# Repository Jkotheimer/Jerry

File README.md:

# Jerry

This is Jerry. A homemade RC toy for my cats to play with. Everything in this repository encapsulates all the technologies used to make this project a reality.

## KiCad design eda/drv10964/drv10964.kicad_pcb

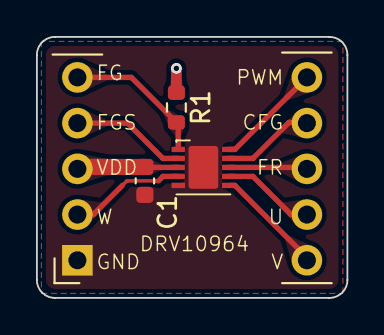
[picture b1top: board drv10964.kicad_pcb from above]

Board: 2 copper layers, 17.2 x 14.5 mm, 5 parts (0 on the bottom side), 10 nets.

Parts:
C1: 2.2uF; C_0603_1608Metric
DRV10964: drv10964
J1, J2: Conn_01x05_Pin; PinHeader_1x05_P2.54mm_Vertical
R1: 100k; R_0603_1608Metric

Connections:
/CFG: DRV10964.9 (CFG), J1.4
/FG: DRV10964.1 (FG), J2.1, R1.2
/FGS: DRV10964.2 (FGS), J2.2
/FR: DRV10964.8 (FR), J1.3
/PWM: DRV10964.10 (PWM), J1.5
/U: DRV10964.7 (U), J1.2
/V: DRV10964.6 (V), J1.1
/W: DRV10964.4 (W), J2.4
GND: C1.2, DRV10964.5 (GND), J2.5
VDD: C1.1, DRV10964.3 (VCC), J2.3, R1.1

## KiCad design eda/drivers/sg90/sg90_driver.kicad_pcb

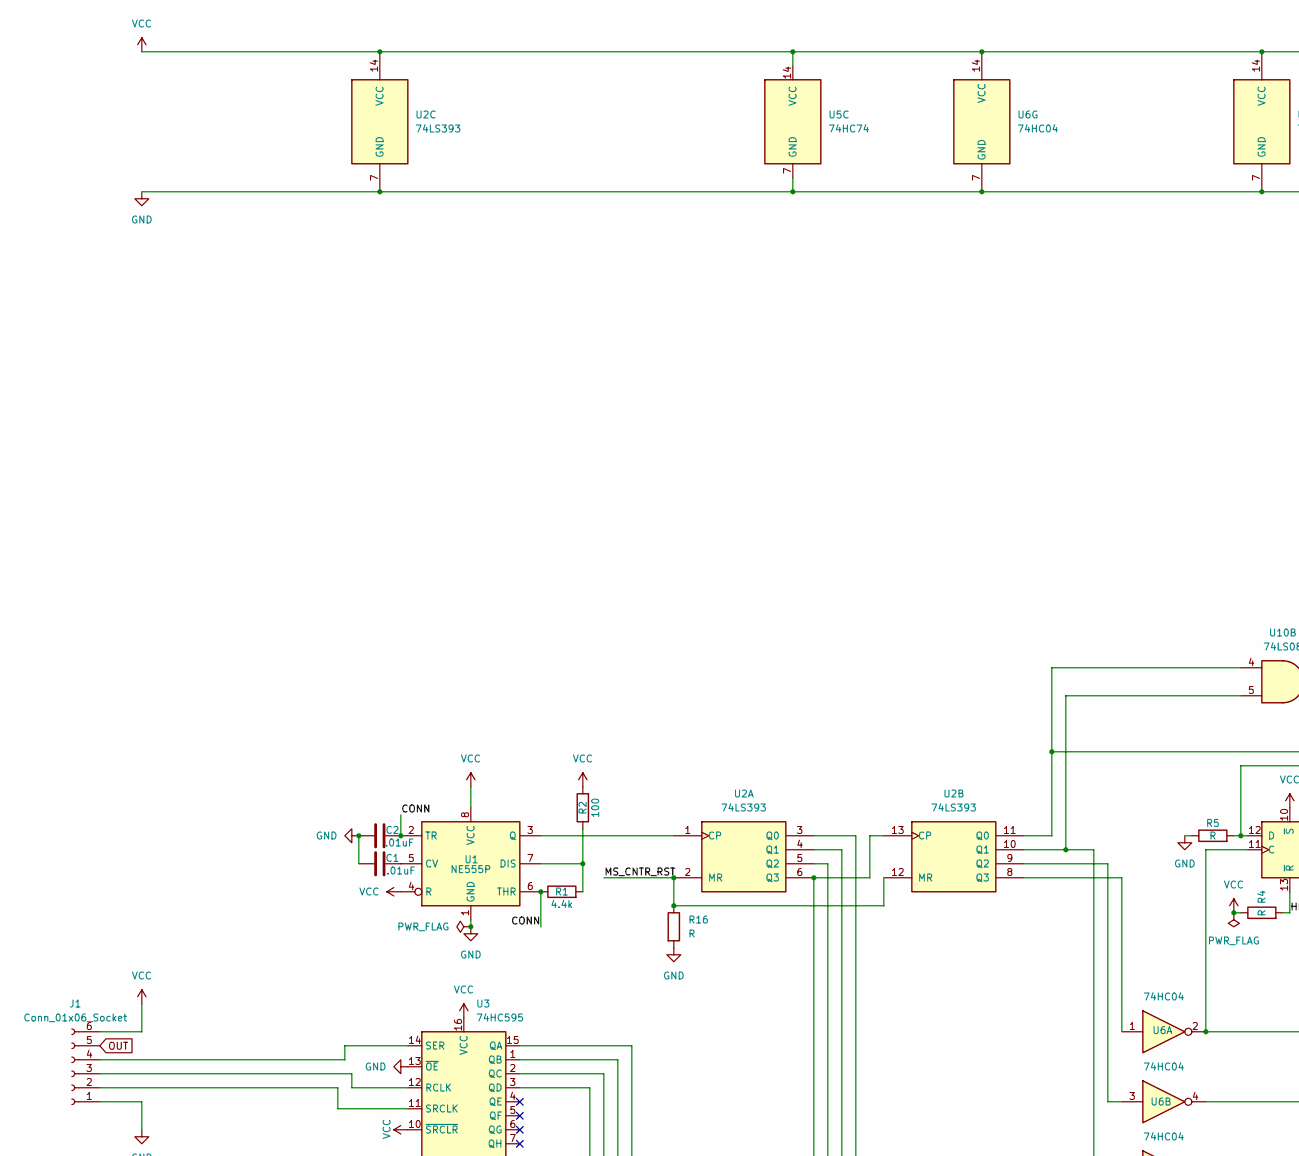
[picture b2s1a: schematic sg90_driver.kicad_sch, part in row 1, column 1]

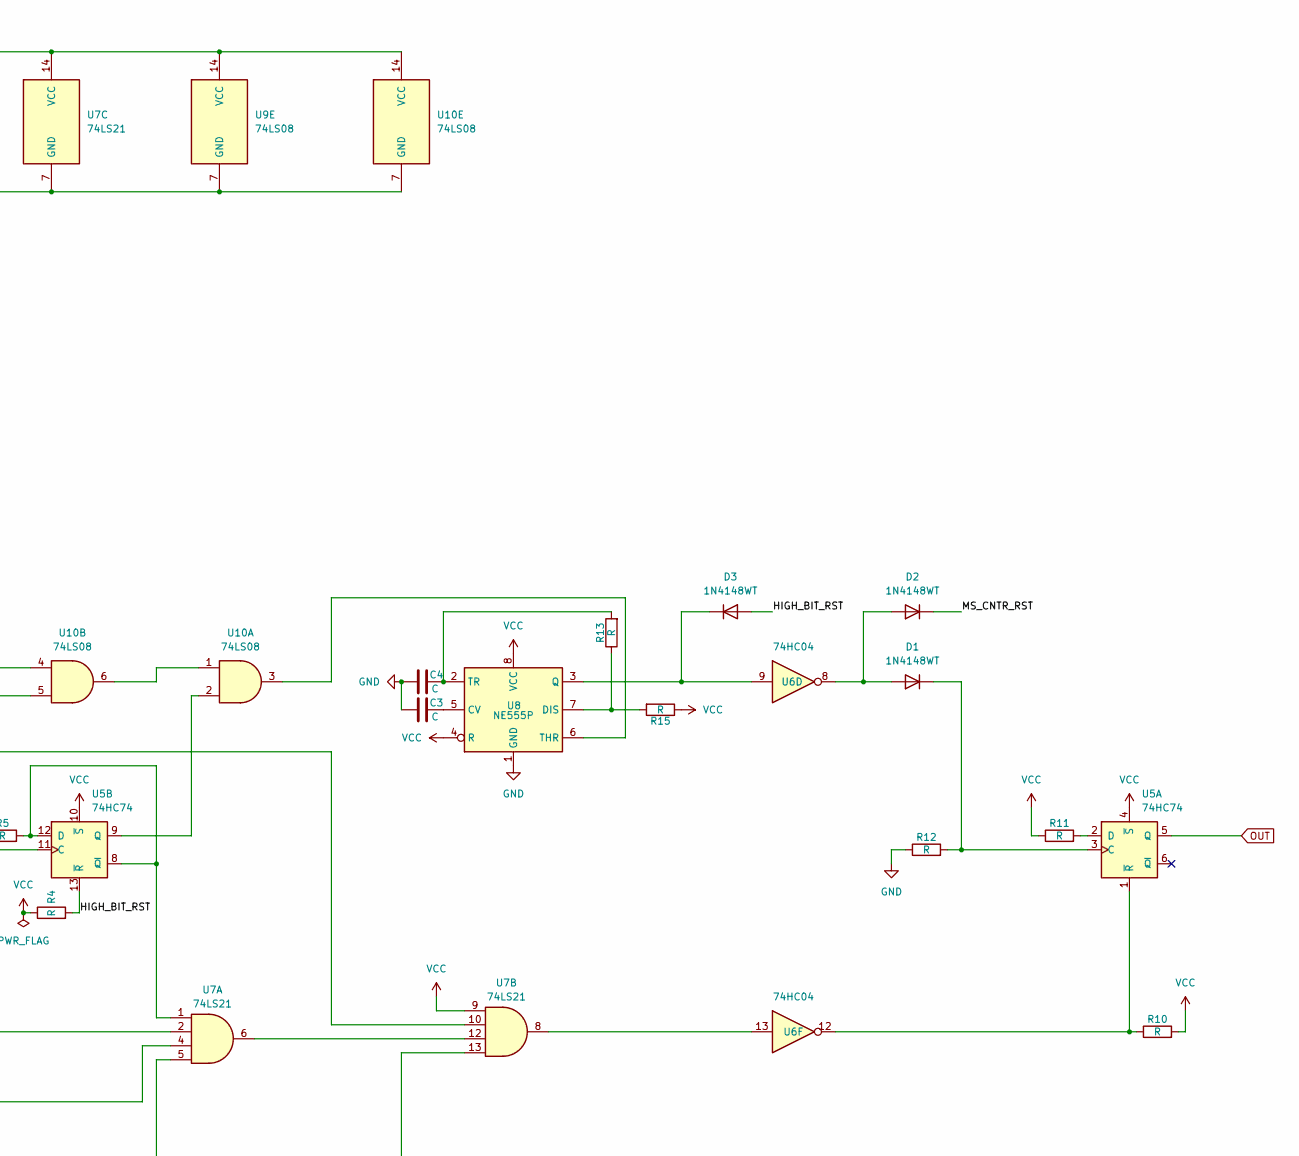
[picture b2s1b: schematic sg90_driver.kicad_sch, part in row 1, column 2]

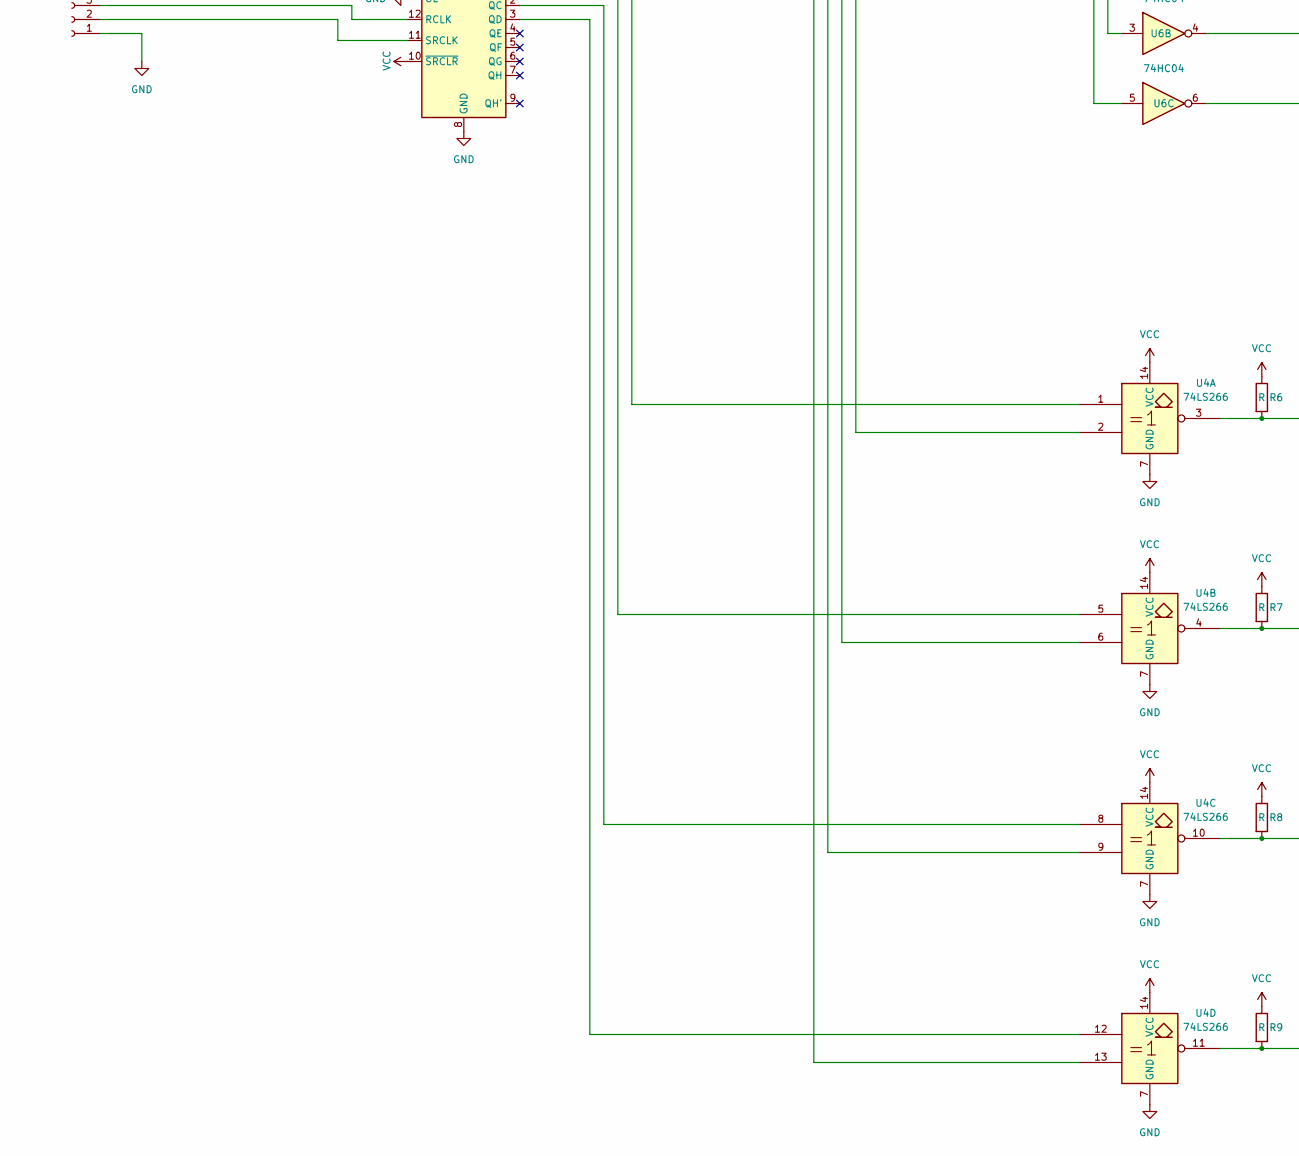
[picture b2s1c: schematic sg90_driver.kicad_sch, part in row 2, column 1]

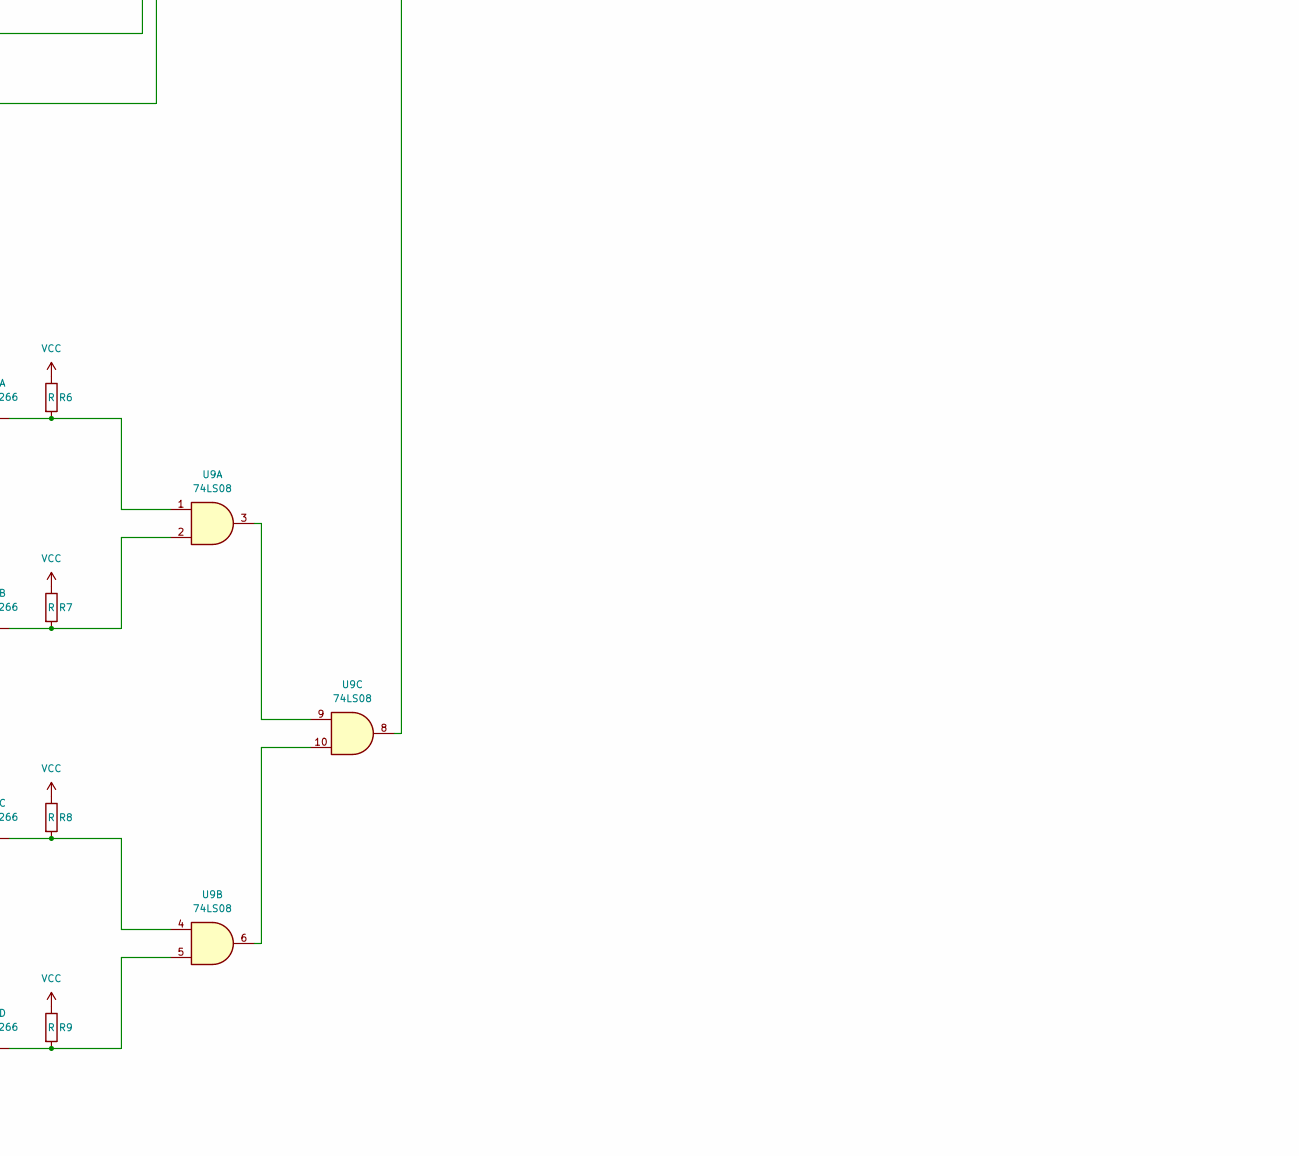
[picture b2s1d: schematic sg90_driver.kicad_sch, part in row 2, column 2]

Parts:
C1, C2: .01uF; C_0603_1608Metric
C3, C4: C; C_0603_1608Metric
D1, D2, D3: 1N4148WT; D_SOD-523
J1: Conn_01x06_Socket; PinHeader_1x06_P2.54mm_Vertical
R1: 4.4k; R_0603_1608Metric
R2: 100; R_0603_1608Metric
R4, R5, R6, R7, R8, R9, R10, R11, R12, R13, R15, R16: R; R_0603_1608Metric
U1, U8: NE555P; SO-8_3.9x4.9mm_P1.27mm
U2: 74LS393; SO-14_3.9x8.65mm_P1.27mm
U3: 74HC595; SO-16_3.9x9.9mm_P1.27mm
U4: 74LS266; SO-14_3.9x8.65mm_P1.27mm
U5: 74HC74; SO-14_3.9x8.65mm_P1.27mm
U6: 74HC04; SO-14_3.9x8.65mm_P1.27mm
U7: 74LS21; SO-14_3.9x8.65mm_P1.27mm
U9, U10: 74LS08; SO-14_3.9x8.65mm_P1.27mm

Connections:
/CONN: C2.1, R1.1, U1.2 (TR), U1.6 (THR)
/HIGH_BIT_RST: D3.2 (A), R4.2, U5.13 (~R)
/MS_CNTR_RST: D2.1 (K), R16.1, U2.2 (MR), U2.12 (MR)
GND: C1.1, C2.2, C3.1, C4.1, J1.1, R5.1, R12.1, R16.2, U1.1 (GND), U2.7 (GND), U3.8 (GND), U3.13 (~OE), U4.7 (GND), U5.7 (GND), U6.7 (GND), U7.7 (GND), U8.1 (GND), U9.7 (GND), U10.7 (GND)
unnamed: D1.2 (A), D2.2 (A), U6.8
unnamed: D1.1 (K), R12.2, U5.3 (C)
unnamed: D3.1 (K), U6.9, U8.3 (Q)
unnamed: J1.2, U3.11 (SRCLK)
unnamed: J1.3, U3.12 (RCLK)
unnamed: J1.4, U3.14 (SER)
unnamed: R6.2, U4.3, U9.1
unnamed: R7.2, U4.4, U9.2
unnamed: R8.2, U4.10, U9.4
unnamed: R9.2, U4.11, U9.5
unnamed: C1.2, U1.5 (CV)
unnamed: R1.2, R2.1, U1.7 (DIS)
unnamed: U1.3 (Q), U2.1 (CP)
unnamed: U2.3 (Q0), U4.2
unnamed: U2.4 (Q1), U4.6
unnamed: U2.5 (Q2), U4.9
unnamed: U2.6 (Q3), U2.13 (CP), U4.13
unnamed: U2.11 (Q0), U7.10, U10.4
unnamed: U2.10 (Q1), U6.5, U10.5
unnamed: U2.9 (Q2), U6.3
unnamed: U2.8 (Q3), U6.1
unnamed: U3.15 (QA), U4.1
unnamed: U3.1 (QB), U4.5
unnamed: U3.2 (QC), U4.8
unnamed: U3.3 (QD), U4.12
unnamed: R11.2, U5.2 (D)
unnamed: R10.1, U5.1 (~R), U6.12
unnamed: U5.11 (C), U6.2, U7.2
unnamed: R5.2, U5.8 (~Q), U5.12 (D), U7.1
unnamed: U5.9 (Q), U10.2
unnamed: U6.4, U7.4
unnamed: U6.6, U7.5
unnamed: U6.13, U7.8
unnamed: U7.6, U7.12
unnamed: U7.13, U9.8
unnamed: C3.2, U8.5 (CV)
unnamed: R13.1, R15.2, U8.7 (DIS)
unnamed: U8.6 (THR), U10.3
unnamed: C4.2, R13.2, U8.2 (TR)
unnamed: U9.3, U9.9
unnamed: U9.6, U9.10
unnamed: U10.1, U10.6
OUT: J1.5, U5.5 (Q)
VCC: J1.6, R2.2, R4.1, R6.1, R7.1, R8.1, R9.1, R10.2, R11.1, R15.1, U1.4 (R), U1.8 (VCC), U2.14 (VCC), U3.10 (~SRCLR), U3.16 (VCC), U4.14 (VCC), U5.4 (~S), U5.10 (~S), U5.14 (VCC), U6.14 (VCC), U7.9, U7.14 (VCC), U8.4 (R), U8.8 (VCC), U9.14 (VCC), U10.14 (VCC)

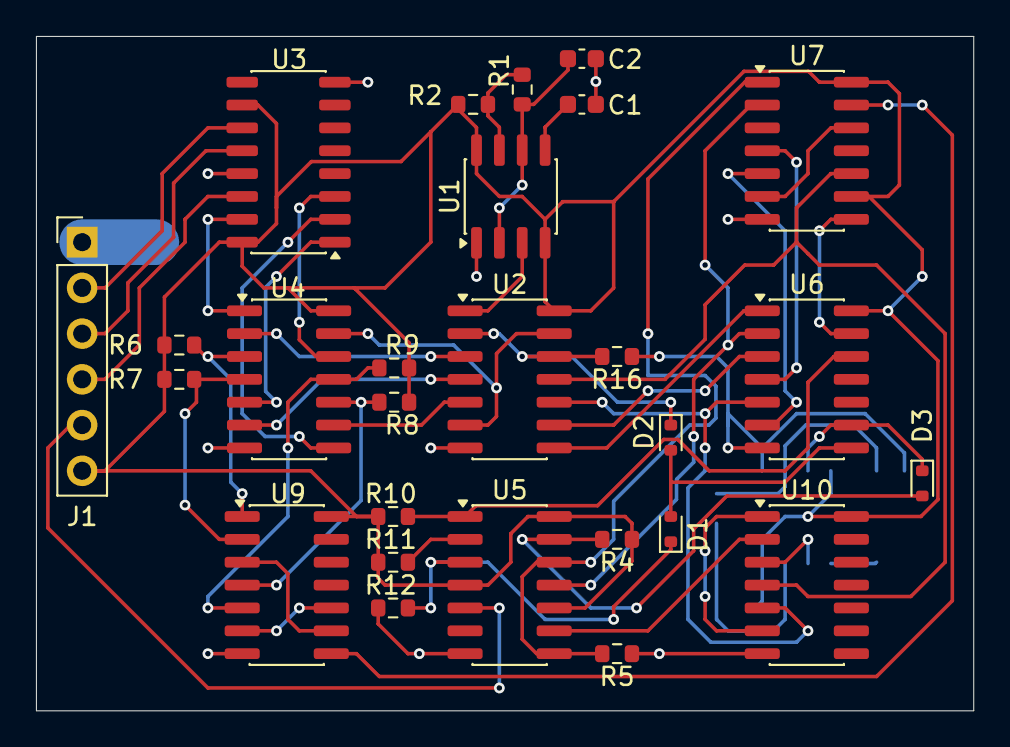
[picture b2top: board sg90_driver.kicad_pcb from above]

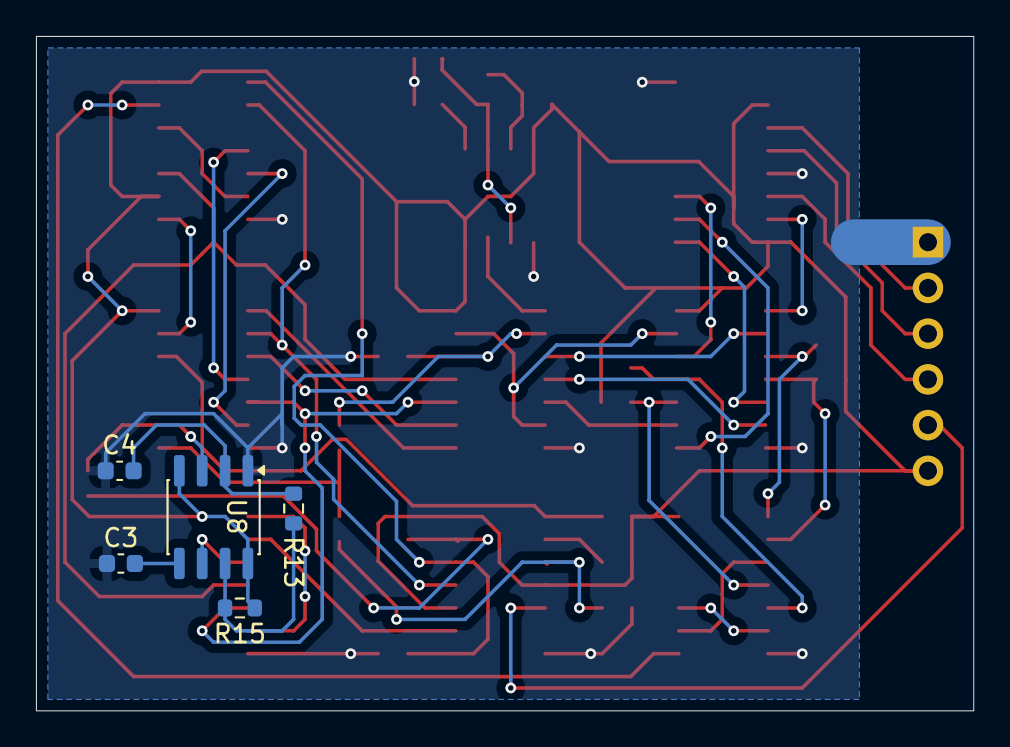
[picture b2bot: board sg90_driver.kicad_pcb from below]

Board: 2 copper layers, 52.1 x 37.5 mm, 32 parts (5 on the bottom side), 48 nets.

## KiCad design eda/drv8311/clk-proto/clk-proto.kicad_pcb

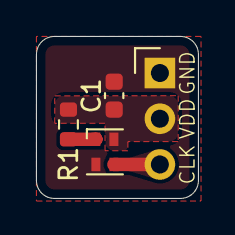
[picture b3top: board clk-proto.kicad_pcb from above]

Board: 2 copper layers, 9.0 x 9.0 mm, 4 parts (0 on the bottom side), 4 nets.

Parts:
C1: C; C_0603_1608Metric
J1: Conn_01x03_Pin; PinHeader_1x03_P2.54mm_Vertical
R1: R; R_0603_1608Metric
Y1: KC2520Z; Oscillator_SMD_Kyocera_KC2520Z-4Pin_2.5x2.0mm

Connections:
GND: C1.1, J1.1, Y1.2 (GND)
unnamed: J1.3, Y1.3 (CLK)
unnamed: R1.2, Y1.1 (INH)
VDD: C1.2, J1.2, R1.1, Y1.4 (VCC)

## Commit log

2023-05-02 Started converting bluetooth service to ble service
2023-08-19 Converted mobile client to a kotlin multi-platform app with ios support
2023-08-19 Added all initial files
2023-12-22 Copied remote and server modules to new repository
2024-02-02 Moved server code to a separate repository
2024-02-02 Renamed ino file
2024-02-02 Added cad models
2024-02-02 Removed unused file
2024-02-04 Updated bracked dimensions and added a setting pin hole
2024-02-04 Updated shaft cap model
2024-02-05 Updated bracket thing
2024-02-05 Updated shaft to include clip. Updated clip to be sturdier
2024-02-08 Renamed wheel-shaft-cap to wheel_shaft_cap
2024-02-08 Added jerry model for the rc car body
2024-02-08 Renamed steering-bracket to steering_bracket
2024-02-08 Added model with raspberry pi generic dimensions & screw hole locations
2024-02-08 Removed model
2025-07-27 Added models and spreadsheetss
2025-07-29 Renamed files
2025-10-11 Started kicad project. kinda messy right now, but will clean up once the pcb is finished
2025-10-11 updated pcb schematic
2025-10-11 test
2025-10-12 Redesigned pcb layout
2025-10-14 Finished custom routing. Needs cleanup.
2025-10-15 Reorganized repository
2025-10-15 Removed unnecessary kicad files
2025-10-15 Added README
2025-10-15 Moved jerry kicad files into drivers/sg90 folder
2025-10-15 Renamed kicad project to sg90_driver
2025-10-15 Updated gitignore to handle new eda directory structure
2025-11-23 Created clock protoboard
2025-11-23 Started drv10964 kicad model
2025-11-24 exported drv10964 gerber files
